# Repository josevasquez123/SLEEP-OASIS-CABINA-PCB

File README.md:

# WNR-CABINA-PCB
Domotic control of LED lights with CAN connection. 

## Topology

Motherboard has internet connection to receive commands by MQTT and then, send instruction by CAN to the boards inside the rooms. The present board is the one that will be placed inside the room.

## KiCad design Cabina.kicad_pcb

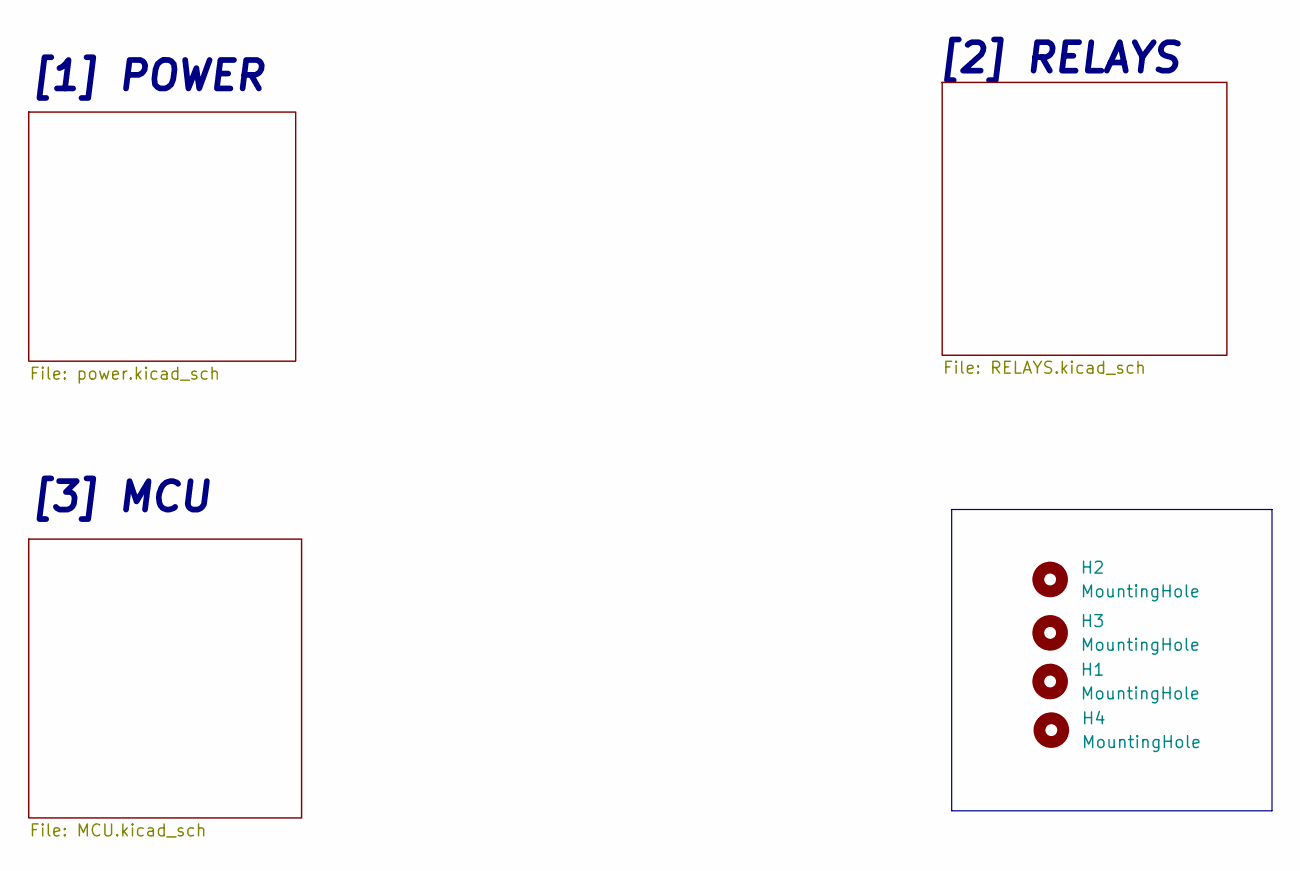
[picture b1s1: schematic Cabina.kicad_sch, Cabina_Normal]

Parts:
H1, H2, H3, H4: MountingHole; MountingHole_3.2mm_M3

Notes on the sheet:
[1] POWER
[2] RELAYS
[3] MCU

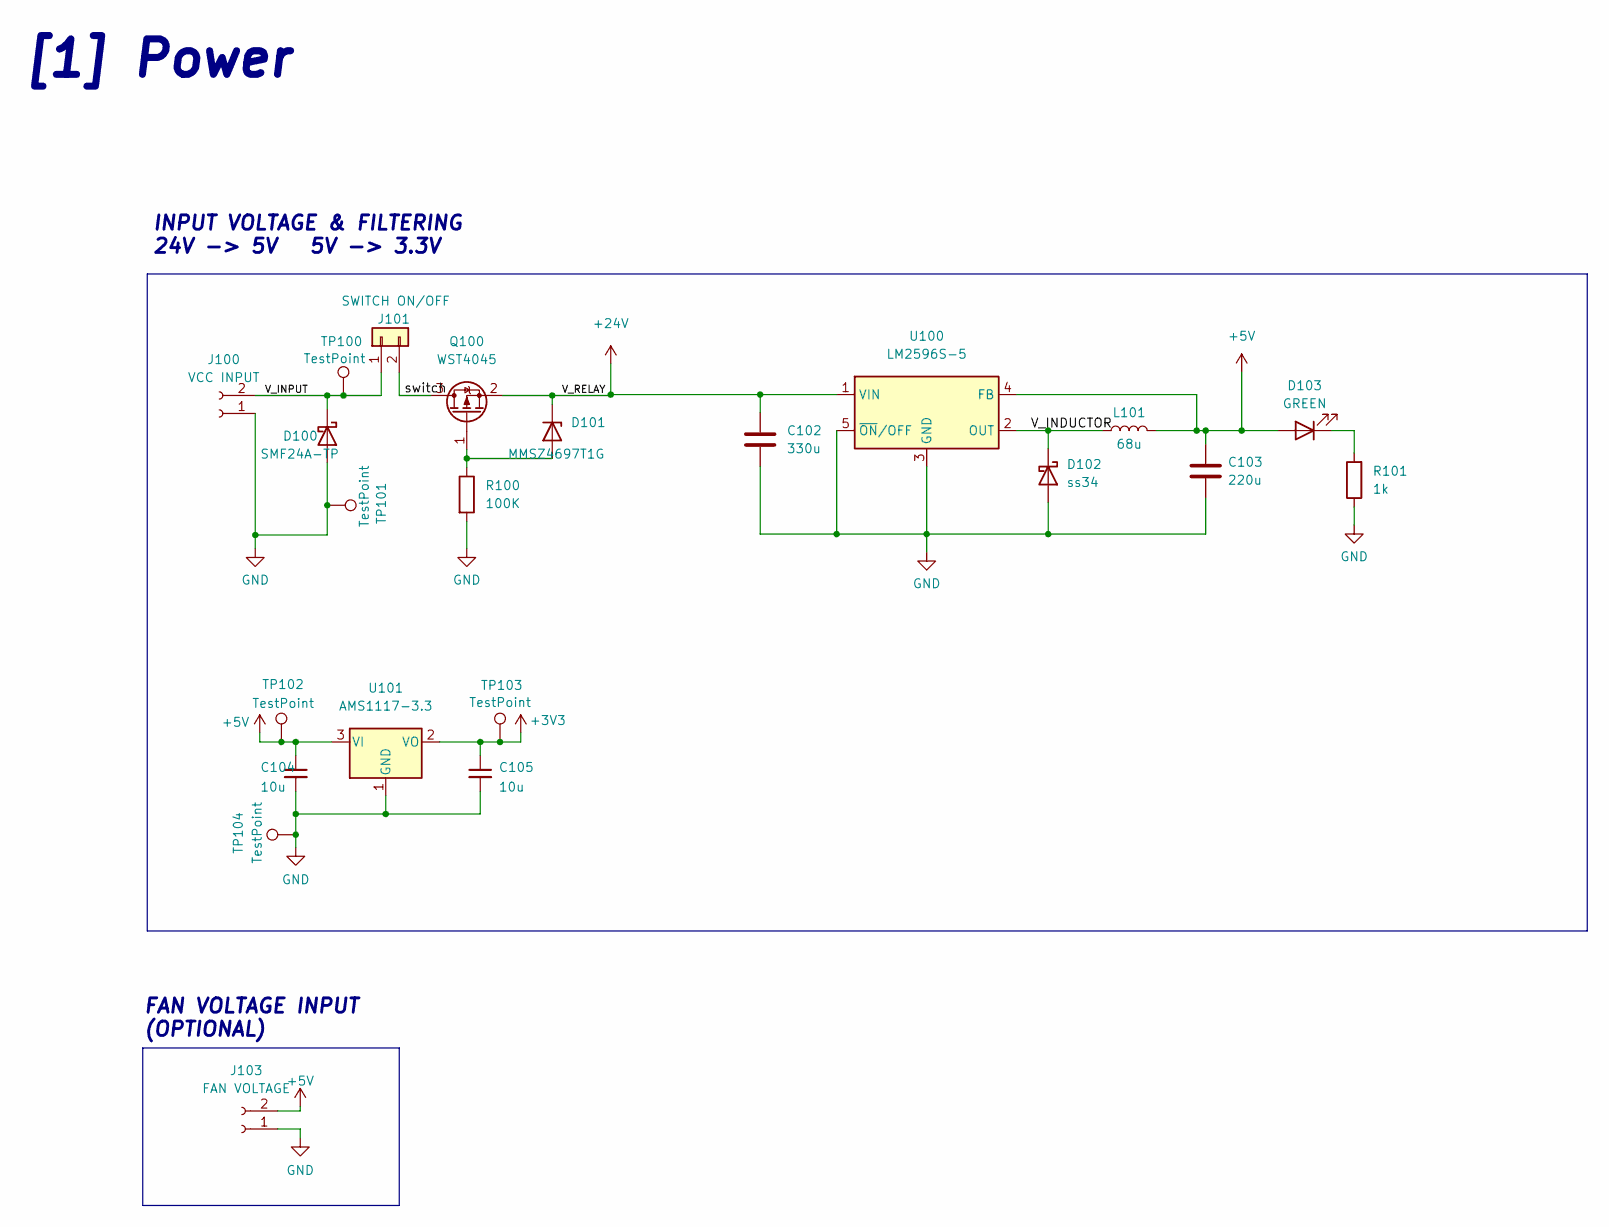
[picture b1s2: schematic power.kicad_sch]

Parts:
C102: 330u; C_Elec_10x10.2; LCSC C239324
C103: 220u; CP_Elec_10x10.5; LCSC C2886113
C104, C105: 10u; C_0805_2012Metric; LCSC C15850
D100: SMF24A-TP; SOD_123FL; LCSC C545276
D101: MMSZ4697T1G; D_SOD-123; LCSC C48870
D102: ss34; D_SMA; LCSC C8678
D103: GREEN; LED_0603_1608Metric; LCSC C72038
J100: VCC INPUT; PhoenixContact_MSTBA_2,5_2-G-5,08_1x02_P5.08mm_Horizontal
J101: SWITCH ON/OFF; JST_B2B-XH-A_LF__SN_
J103: FAN VOLTAGE; PinHeader_1x02_P2.54mm_Vertical
L101: 68u; SMD_12.3X12.3mm; LCSC C2929504
Q100: WST4045; SOT-23; LCSC C719073
R100: 100K; R_1206_3216Metric; LCSC C17900
R101: 1k; R_0603_1608Metric; LCSC C21190
TP100, TP101, TP102, TP103, TP104: TestPoint; TestPoint_Pad_D2.0mm
U100: LM2596S-5; TO-263-5_TabPin3; LCSC C10002
U101: AMS1117-3.3; SOT-223-3_TabPin2; LCSC C6186

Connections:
+3V3: C105.1, TP103.1, U101.2 (VO); also elsewhere on the board
+5V: C103.1, C104.1, D103.2 (A), J103.2, L101.2, TP102.1, U100.4 (FB), U101.3 (VI); also elsewhere on the board
+24V: C102.1, D101.1 (K), Q100.2 (S), U100.1 (VIN); also elsewhere on the board
/POWER/V_INDUCTOR: D102.1 (K), L101.1, U100.2 (OUT)
/POWER/V_INPUT: D100.1 (K), J100.2, J101.1, TP100.1
/POWER/switch: J101.2, Q100.3 (D)
GND: C102.2, C103.2, C104.2, C105.2, D100.2 (A), D102.2 (A), J100.1, J103.1, R100.2, R101.1, TP101.1, TP104.1, U100.3 (GND), U100.5 (~ON/OFF), U101.1 (GND); also elsewhere on the board
unnamed: D101.2 (A), Q100.1 (G), R100.1
unnamed: D103.1 (K), R101.2

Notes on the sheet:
[1] Power
INPUT VOLTAGE & FILTERING 24V -> 5V 5V -> 3.3V
FAN VOLTAGE INPUT (OPTIONAL)

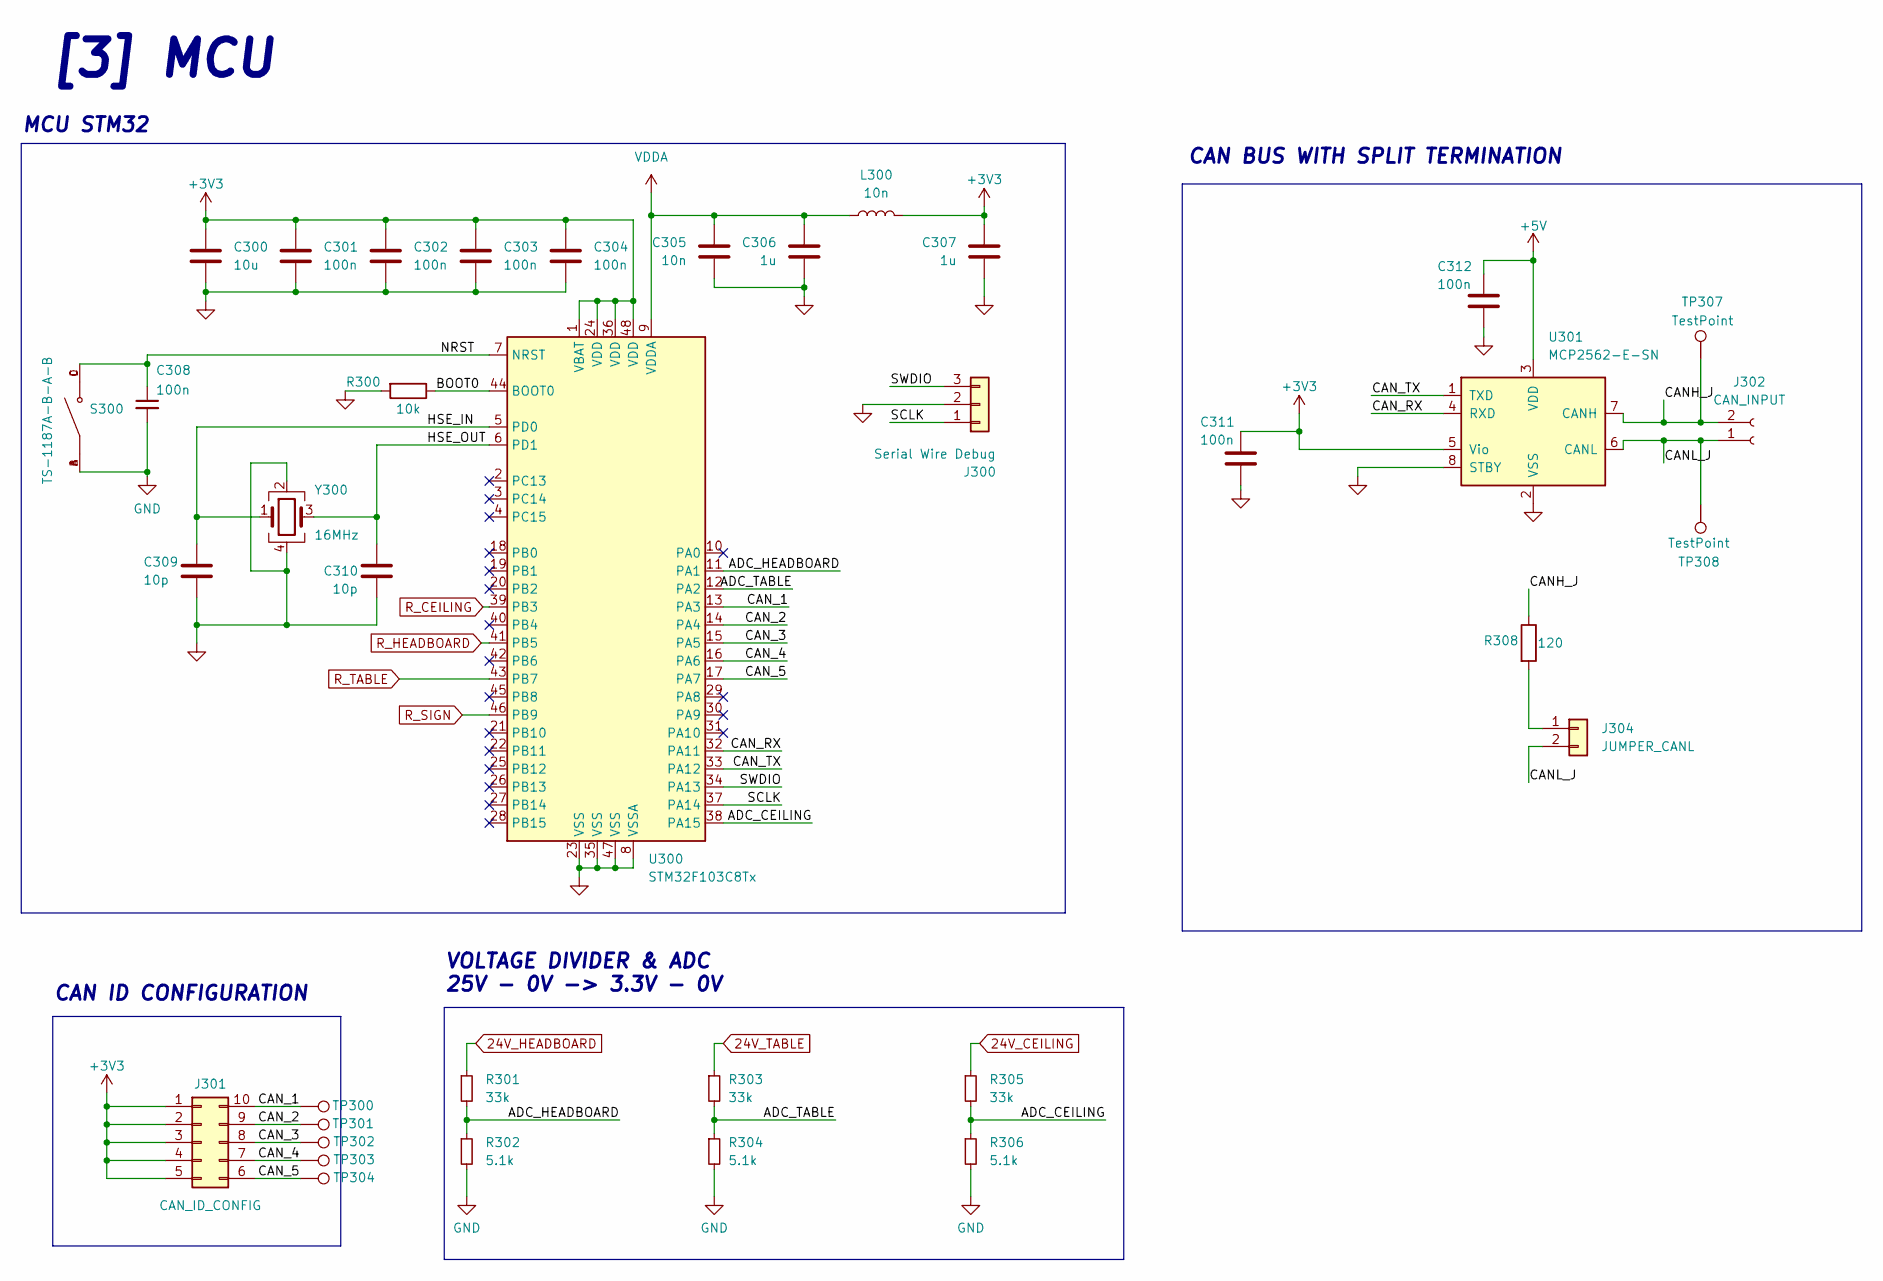
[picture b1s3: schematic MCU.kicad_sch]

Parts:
C300: 10u; C_0603_1608Metric; LCSC C19702
C301, C302, C303, C304, C308, C311, C312: 100n; C_0402_1005Metric; LCSC C1525
C305: 10n; C_0402_1005Metric; LCSC C15195
C306, C307: 1u; C_0603_1608Metric; LCSC C15849
C309, C310: 10p; C_0402_1005Metric; LCSC C32949
J300: Serial Wire Debug; PinSocket_1x03_P2.54mm_Vertical
J301: CAN_ID_CONFIG; SW_DIP_SPSTx05_Slide_9.78x14.88mm_W7.62mm_P2.54mm
J302: CAN_INPUT; PhoenixContact_MSTBA_2,5_2-G-5,08_1x02_P5.08mm_Horizontal
J304: JUMPER_CANL; PinHeader_1x02_P2.54mm_Vertical
L300: 10n; L_0603_1608Metric; LCSC C913709
R300: 10k; R_0402_1005Metric; LCSC C25744
R301, R303, R305: 33k; R_0805_2012Metric; LCSC C17633
R302, R304, R306: 5.1k; R_0805_2012Metric; LCSC C27834
R308: 120; R_0805_2012Metric; LCSC C17437
S300: TS-1187A-B-A-B; SWITCH_SMD; LCSC C318884
TP300, TP301, TP302, TP303, TP304, TP307, TP308: TestPoint; TestPoint_Pad_D2.0mm
U300: STM32F103C8Tx; LQFP-48_7x7mm_P0.5mm; LCSC C8734
U301: MCP2562-E-SN; SOIC-8_3.9x4.9mm_P1.27mm; LCSC C191417
Y300: 16MHz; Crystal_SMD_3225-4Pin_3.2x2.5mm; LCSC C13738

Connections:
24V_CEILING: R305.1; also elsewhere on the board
24V_HEADBOARD: R301.1; also elsewhere on the board
24V_TABLE: R303.1; also elsewhere on the board
+3V3: C300.1, C301.1, C302.1, C303.1, C304.1, C307.1, C311.1, J301.1, J301.2, J301.3, J301.4, J301.5, L300.2, U300.1 (VBAT), U300.24 (VDD), U300.36 (VDD), U300.48 (VDD), U301.5 (Vio); also elsewhere on the board
+5V: C312.1, U301.3 (VDD); also elsewhere on the board
/MCU/ADC_CEILING: R305.2, R306.1, U300.38 (PA15)
/MCU/ADC_HEADBOARD: R301.2, R302.1, U300.11 (PA1)
/MCU/ADC_TABLE: R303.2, R304.1, U300.12 (PA2)
/MCU/BOOT0: R300.1, U300.44 (BOOT0)
/MCU/CANH_J: J302.2, R308.1, TP307.1, U301.7 (CANH)
/MCU/CANL_J: J302.1, J304.2, TP308.1, U301.6 (CANL)
/MCU/CAN_1: J301.10, TP300.1, U300.13 (PA3)
/MCU/CAN_2: J301.9, TP301.1, U300.14 (PA4)
/MCU/CAN_3: J301.8, TP302.1, U300.15 (PA5)
/MCU/CAN_4: J301.7, TP303.1, U300.16 (PA6)
/MCU/CAN_5: J301.6, TP304.1, U300.17 (PA7)
/MCU/CAN_RX: U300.32 (PA11), U301.4 (RXD)
/MCU/CAN_TX: U300.33 (PA12), U301.1 (TXD)
/MCU/HSE_IN: C309.1, U300.5 (PD0), Y300.1
/MCU/HSE_OUT: C310.1, U300.6 (PD1), Y300.3
/MCU/NRST: C308.1, S300.C, S300.D, U300.7 (NRST)
/MCU/SCLK: J300.1, U300.37 (PA14)
/MCU/SWDIO: J300.3, U300.34 (PA13)
GND: C300.2, C301.2, C302.2, C303.2, C304.2, C305.2, C306.2, C307.2, C308.2, C309.2, C310.2, C311.2, C312.2, J300.2, R300.2, R302.2, R304.2, R306.2, S300.A, S300.B, U300.8 (VSSA), U300.23 (VSS), U300.35 (VSS), U300.47 (VSS), U301.2 (VSS), U301.8 (STBY), Y300.2, Y300.4; also elsewhere on the board
unnamed: J304.1, R308.2
R_CEILING: U300.39 (PB3); also elsewhere on the board
R_HEADBOARD: U300.41 (PB5); also elsewhere on the board
R_SIGN: U300.46 (PB9); also elsewhere on the board
R_TABLE: U300.43 (PB7); also elsewhere on the board
VDDA: C305.1, C306.1, L300.1, U300.9 (VDDA)

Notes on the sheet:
CAN ID CONFIGURATION
VOLTAGE DIVIDER & ADC 25V - 0V -> 3.3V - 0V
CAN BUS WITH SPLIT TERMINATION
[3] MCU
MCU STM32

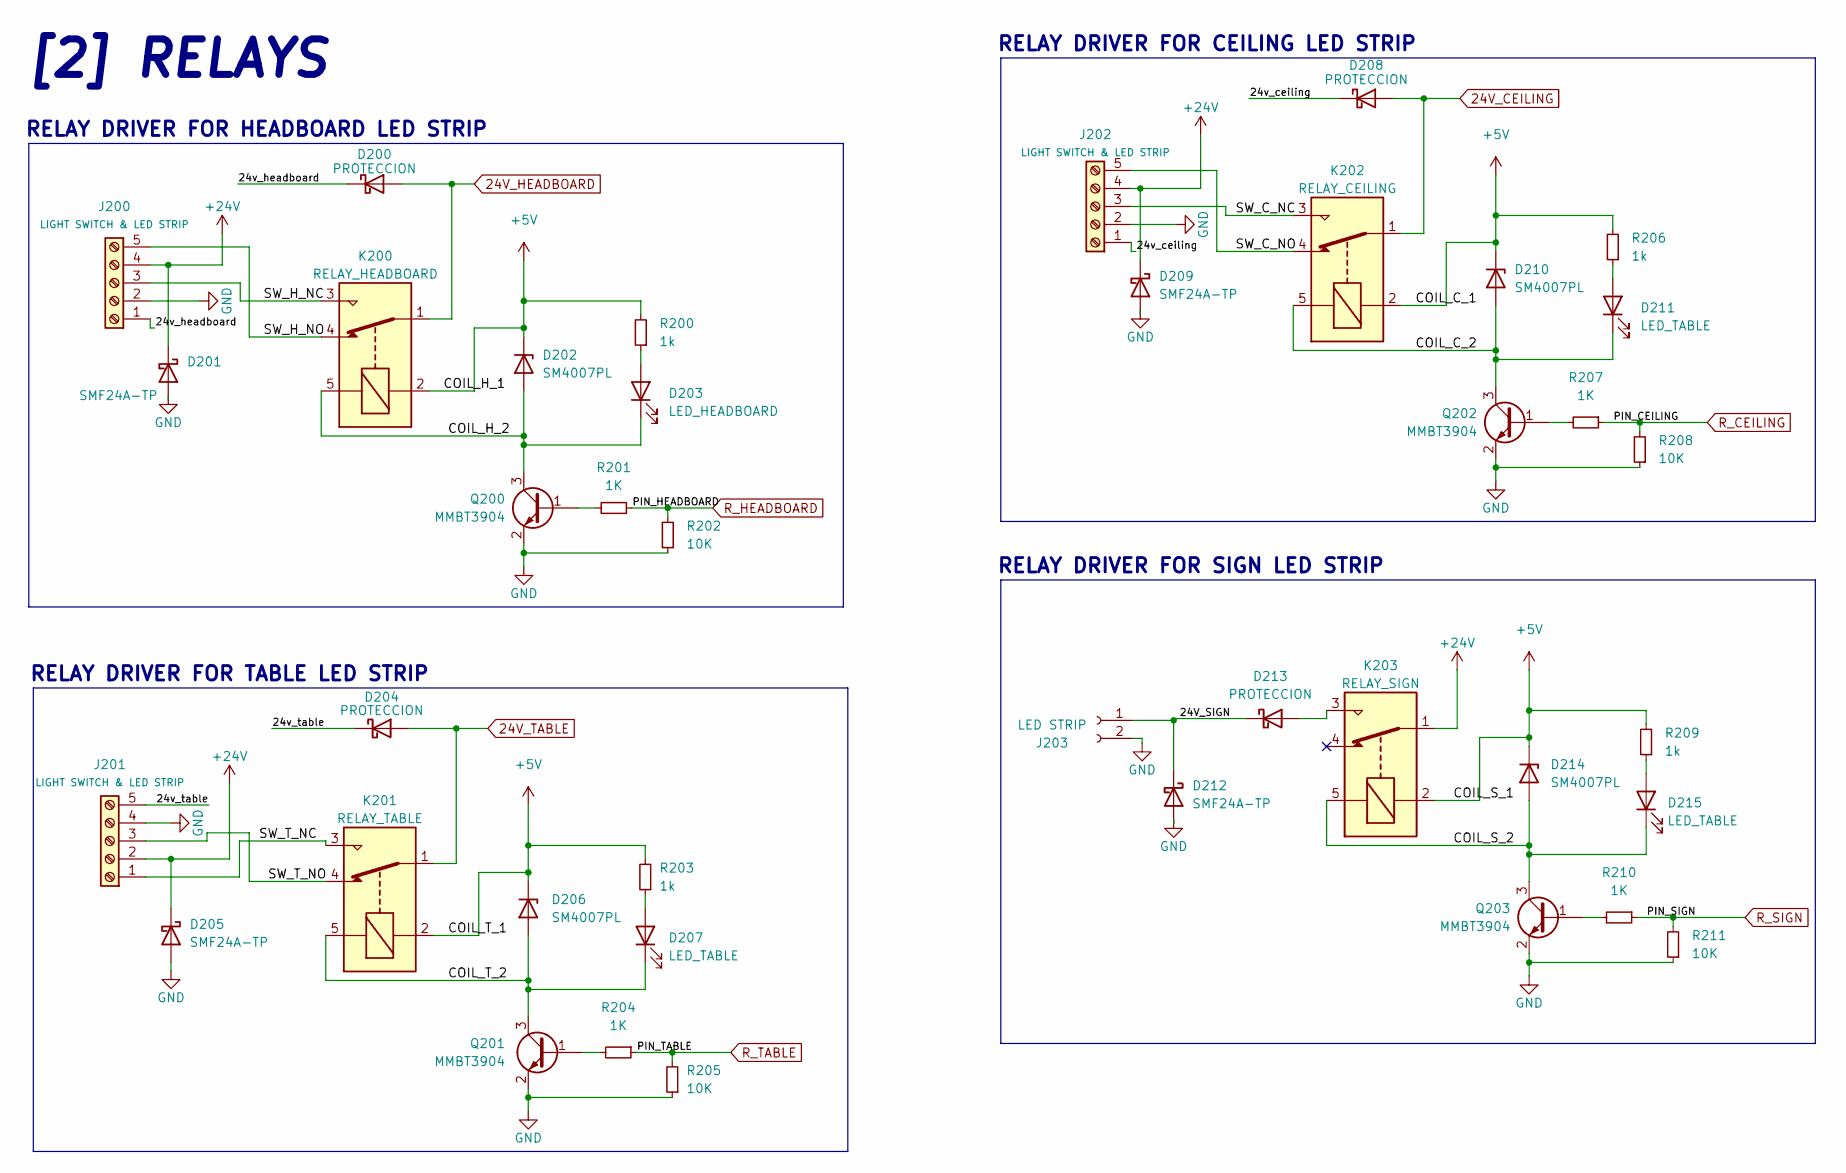
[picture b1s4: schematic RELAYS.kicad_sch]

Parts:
D200, D204, D208, D213: PROTECCION; Nexperia_CFP3_SOD-123W; LCSC C552879
D201, D205, D209, D212: SMF24A-TP; SOD_123FL; LCSC C545276
D202, D206, D210, D214: SM4007PL; SOD_123FL; LCSC C64898
D203: LED_HEADBOARD; LED_0603_1608Metric; LCSC C72038
D207, D211, D215: LED_TABLE; LED_0603_1608Metric; LCSC C72038
J200, J201, J202: LIGHT SWITCH & LED STRIP; PhoenixContact_MSTBA_2,5_5-G-5,08_1x05_P5.08mm_Horizontal
J203: LED STRIP; PhoenixContact_MSTBA_2,5_2-G-5,08_1x02_P5.08mm_Horizontal
K200: RELAY_HEADBOARD; Relay_SPDT_Finder_36.11
K201: RELAY_TABLE; Relay_SPDT_Finder_36.11
K202: RELAY_CEILING; Relay_SPDT_Finder_36.11
K203: RELAY_SIGN; Relay_SPDT_Finder_36.11
Q200, Q201, Q202, Q203: MMBT3904; SOT-23; LCSC C20526
R200, R203, R206, R209: 1k; R_0603_1608Metric; LCSC C21190
R201, R204, R207, R210: 1K; R_0603_1608Metric; LCSC C21190
R202, R205, R208, R211: 10K; R_0603_1608Metric; LCSC C25804

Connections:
24V_CEILING: D208.2 (A), K202.1; also elsewhere on the board
24V_HEADBOARD: D200.2 (A), K200.1; also elsewhere on the board
24V_TABLE: D204.2 (A), K201.1; also elsewhere on the board
+5V: D202.1 (K), D206.1 (K), D210.1 (K), D214.1 (K), K200.2, K201.2, K202.2, K203.2, R200.2, R203.2, R206.2, R209.2; also elsewhere on the board
+24V: D201.1 (K), D205.1 (K), D209.1 (K), J200.4, J201.2, J202.4, K203.1; also elsewhere on the board
/RELAYS/24V_SIGN: D212.1 (K), D213.1 (K), J203.1
/RELAYS/24v_ceiling: D208.1 (K), J202.1
/RELAYS/24v_headboard: D200.1 (K), J200.1
/RELAYS/24v_table: D204.1 (K), J201.5
/RELAYS/COIL_C_2: D210.2 (A), D211.1 (K), K202.5, Q202.3 (C)
/RELAYS/COIL_H_2: D202.2 (A), D203.1 (K), K200.5, Q200.3 (C)
/RELAYS/COIL_S_2: D214.2 (A), D215.1 (K), K203.5, Q203.3 (C)
/RELAYS/COIL_T_2: D206.2 (A), D207.1 (K), K201.5, Q201.3 (C)
/RELAYS/SW_C_NC: J202.3, K202.3
/RELAYS/SW_C_NO: J202.5, K202.4
/RELAYS/SW_H_NC: J200.3, K200.3
/RELAYS/SW_H_NO: J200.5, K200.4
/RELAYS/SW_T_NC: J201.1, K201.3
/RELAYS/SW_T_NO: J201.3, K201.4
GND: D201.2 (A), D205.2 (A), D209.2 (A), D212.2 (A), J200.2, J201.4, J202.2, J203.2, Q200.2 (E), Q201.2 (E), Q202.2 (E), Q203.2 (E), R202.1, R205.1, R208.1, R211.1; also elsewhere on the board
unnamed: D203.2 (A), R200.1
unnamed: D207.2 (A), R203.1
unnamed: D211.2 (A), R206.1
unnamed: D213.2 (A), K203.3
unnamed: D215.2 (A), R209.1
unnamed: Q200.1 (B), R201.2
unnamed: Q201.1 (B), R204.2
unnamed: Q202.1 (B), R207.2
unnamed: Q203.1 (B), R210.2
R_CEILING: R207.1, R208.2; also elsewhere on the board
R_HEADBOARD: R201.1, R202.2; also elsewhere on the board
R_SIGN: R210.1, R211.2; also elsewhere on the board
R_TABLE: R204.1, R205.2; also elsewhere on the board

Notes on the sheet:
RELAY DRIVER FOR HEADBOARD LED STRIP
RELAY DRIVER FOR TABLE LED STRIP
[2] RELAYS
RELAY DRIVER FOR CEILING LED STRIP
RELAY DRIVER FOR SIGN LED STRIP

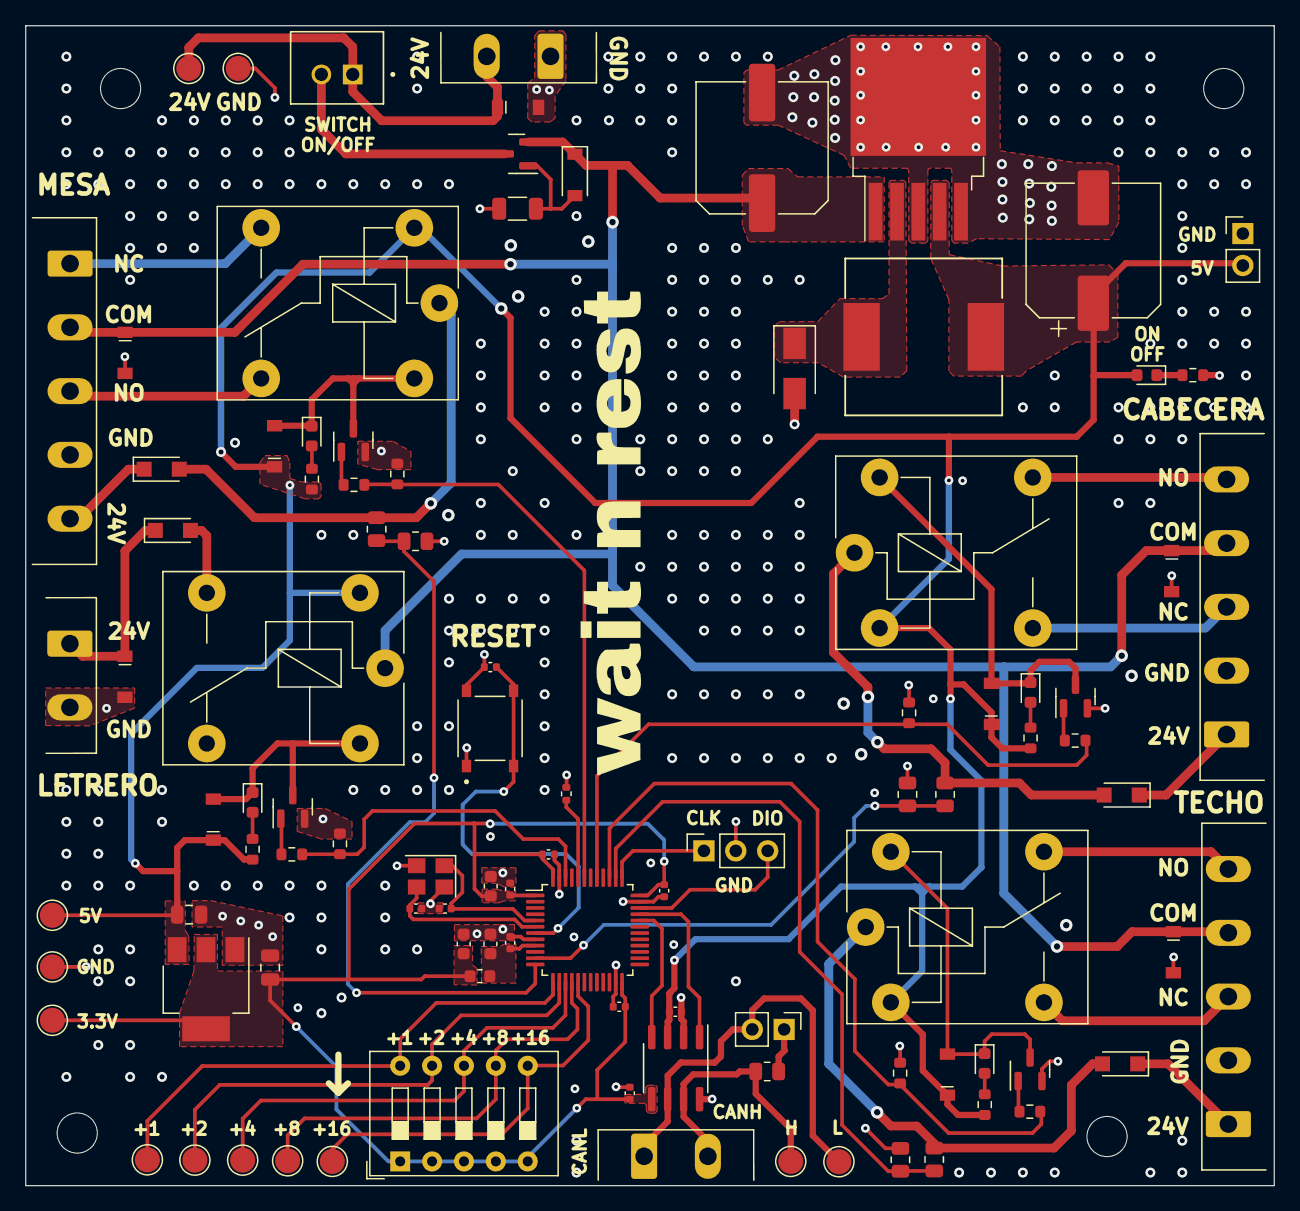
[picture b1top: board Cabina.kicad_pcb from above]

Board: 4 copper layers, 99.5 x 92.4 mm, 103 parts (0 on the bottom side), 59 nets.

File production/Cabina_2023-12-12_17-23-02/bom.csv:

Designator,Footprint,Quantity,Value,LCSC Part #
C102,C_Elec_10x10.2,1,330u,C239324
C103,CP_Elec_10x10.5,1,220u,C2886113
"C104, C105",0805,2,10u,C15850
C300,0603,1,10u,C19702
"C301, C302, C303, C304, C308, C311, C312",0402,7,100n,C1525
C305,0402,1,10n,C15195
"C306, C307",0603,2,1u,C15849
"C309, C310",0402,2,10p,C32949
"D100, D201, D205, D209, D212",SOD_123FL,5,SMF24A-TP,C545276
D101,D_SOD-123,1,MMSZ4697T1G,C48870
D102,D_SMA,1,ss34,C8678
D103,0603,1,GREEN,C72043
"D200, D204, D208, D213",D_SOD-128,4,PROTECCION, C513108
"D202, D206, D210, D214",SOD_123FL,4,SM4007PL,C64898
D203,0603,1,LED_HEADBOARD,C72038
"D207, D211, D215",0603,3,LED_TABLE,C72038
"H1, H2, H3, H4",MountingHole_3.2mm_M3,4,MountingHole,
J100,"PhoenixContact_MSTBA_2,5_2-G-5,08_1x02_P5.08mm_Horizontal",1,VCC INPUT,
J101,PinHeader_1x02_P2.54mm_Vertical,1,SWITCH ON/OFF,
J103,PinHeader_1x02_P2.54mm_Vertical,1,FAN VOLTAGE,
"J200, J201, J202","PhoenixContact_MSTBA_2,5_5-G-5,08_1x05_P5.08mm_Horizontal",3,LIGHT SWITCH & LED STRIP,
J203,"PhoenixContact_MSTBA_2,5_2-G-5,08_1x02_P5.08mm_Horizontal",1,LED STRIP,
J300,PinSocket_1x03_P2.54mm_Vertical,1,Serial Wire Debug,
J301,SW_DIP_SPSTx05_Slide_9.78x14.88mm_W7.62mm_P2.54mm,1,CAN_ID_CONFIG,
J302,"PhoenixContact_MSTBA_2,5_2-G-5,08_1x02_P5.08mm_Horizontal",1,CAN_INPUT,
J304,PinHeader_1x02_P2.54mm_Vertical,1,JUMPER_CANL,
K200,Relay_SPDT_Finder_36.11,1,RELAY_HEADBOARD,
K201,Relay_SPDT_Finder_36.11,1,RELAY_TABLE,
K202,Relay_SPDT_Finder_36.11,1,RELAY_CEILING,
K203,Relay_SPDT_Finder_36.11,1,RELAY_SIGN,
L101,SMD_12.3X12.3mm,1,68u,C2929504
L300,0603,1,10n,C913709
Q100,SOT-23,1,WST4045,C719073
"Q200, Q201, Q202, Q203",SOT-23,4,MMBT3904,C20526
R100,1206,1,100K,C17900
"R101, R200, R201, R203, R204, R206, R207, R209, R210",0603,9,1k,C21190
"R202, R205, R208, R211",0603,4,10K,C25804
R300,0402,1,10k,C25744
"R301, R303, R305",0805,3,33k,C17633
"R302, R304, R306",0805,3,5.1k,C27834
R308,0805,1,120,C17437
S300,SWITCH_SMD,1,TS-1187A-B-A-B,C318884
"TP100, TP101, TP102, TP103, TP104, TP300, TP301, TP302, TP303, TP304, TP307, TP308",TestPoint_Pad_D2.0mm,12,TestPoint,
U100,TO-263-5_TabPin3,1,LM2596S-5,C10002
U101,SOT-223-3_TabPin2,1,AMS1117-3.3,C6186
U300,LQFP-48_7x7mm_P0.5mm,1,STM32F103C8Tx,C8734
U301,SOIC-8_3.9x4.9mm_P1.27mm,1,MCP2562-E-SN,C191417
Y300,Crystal_SMD_3225-4Pin_3.2x2.5mm,1,16MHz,C13738

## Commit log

2023-12-20 change board stackup
2024-02-19 version validada
